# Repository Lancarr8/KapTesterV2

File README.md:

# ⚡ KapTester V2

> Capacitance Tester — ATmega328P based custom PCB project  
> Built as **AP2 (Abschlussprüfung Teil 2)** — Vocational exam project 🇩🇪

---

## 📷 Photos
*Coming soon – V2 build photos*

---

## 📖 About

The **KapTester V2** is a custom-built capacitance measurement device based on the ATmega328P microcontroller. It was designed and built from scratch as part of a vocational training exam (IHK AP2), covering all phases from schematic design to PCB manufacturing and firmware development.

---

## ⚙️ Hardware

| Component | Details |
|-----------|---------|
| MCU | ATmega328P @ 16MHz |
| Display | SSD1306 OLED 128x64 (I2C) |
| Voltage Reg | LM317 (1.2V – 32V adjustable) |
| PCB | Custom 2-layer, manufactured by PCBWay |
| Power | USB (5V) |
| Interface | Tactile button, screw terminals |

---

## 💾 Firmware

Three firmware versions were developed during the project:

| Version | Folder | Description |
|---------|--------|-------------|
| FW1 | `fw1_produktion` | Production firmware – stable release |
| FW2 | `fw2_test` | Test firmware – debugging & measurement testing |
| FW3 | `fw3_Voll` | Full feature firmware – all functions enabled |

### 🔧 Flashing

```bash
# Flash production firmware via avrdude
avrdude -c usbasp -p m328p -U flash:w:fw1_produktion/kaptester.hex:i
```

---

## 📁 Repository Structure

```
KapTesterV2/
├── Firmware/
│   ├── fw1_produktion/     # Production firmware (main.c, .hex, .elf)
│   ├── fw2_test/           # Test firmware
│   └── fw3_Voll/           # Full firmware
├── KiCad KapTester V2/
│   ├── KapTesterV2.kicad_sch   # Schematic
│   ├── KapTesterV2.kicad_pcb   # PCB layout
│   └── GerberV2/               # Gerber files for manufacturing
├── Dokumente/              # Project documentation (German)
│   └── Phasen/             # Phase documentation (Info/Plan/Build/Evaluate)
└── Präsentation/           # Final exam presentation (PPTX + PDF)
```

---

## 🛠️ Tools Used

- **AVR-GCC** – Firmware compilation
- **avrdude** – Flashing
- **KiCad 8** – Schematic & PCB design
- **PCBWay** – PCB manufacturing

---

## 📄 License

MIT License – feel free to use, modify and build upon this project.

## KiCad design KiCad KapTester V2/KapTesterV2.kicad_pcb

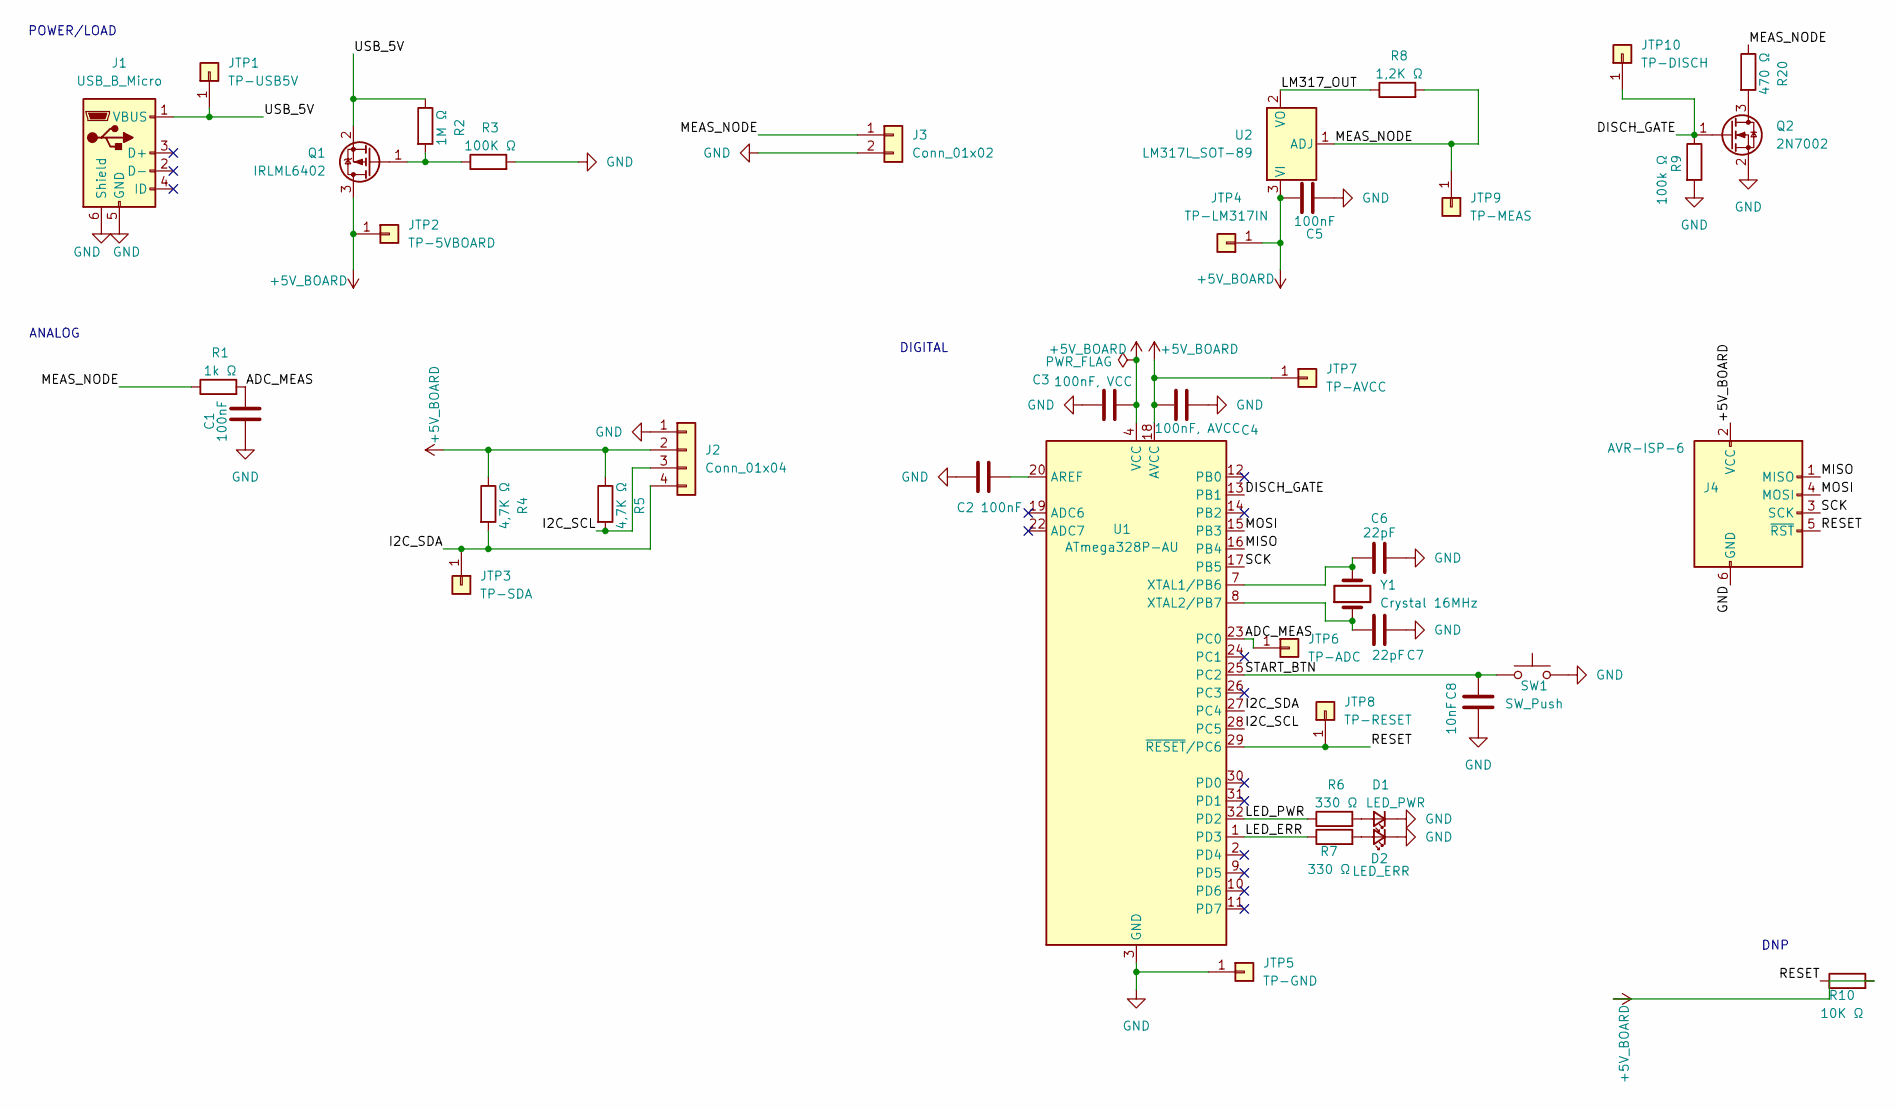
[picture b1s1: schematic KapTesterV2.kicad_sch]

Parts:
C1, C2, C5: 100nF; C_0805_2012Metric_Pad1.18x1.45mm_HandSolder
C3: 100nF, VCC; C_0805_2012Metric_Pad1.18x1.45mm_HandSolder
C4: 100nF, AVCC; C_0805_2012Metric_Pad1.18x1.45mm_HandSolder
C6, C7: 22pF; C_Disc_D3.4mm_W2.1mm_P2.50mm
C8: 10nF; C_0805_2012Metric_Pad1.18x1.45mm_HandSolder
D1: LED_PWR; LED_D5.0mm
D2: LED_ERR; LED_D5.0mm
J1: USB_B_Micro; USB_Micro-B_Molex_47346-0001
J2: Conn_01x04; PinHeader_1x04_P2.54mm_Vertical
J3: Conn_01x02; TerminalBlock_Phoenix_MKDS-1,5-2-5.08_1x02_P5.08mm_Horizont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
J4: AVR-ISP-6; PinHeader_2x03_P2.54mm_Vertical
JTP1: TP-USB5V; PinHeader_1x01_P2.54mm_Vertical
JTP2: TP-5VBOARD; PinHeader_1x01_P2.54mm_Vertical
JTP3: TP-SDA; PinHeader_1x01_P2.54mm_Vertical
JTP4: TP-LM317IN; PinHeader_1x01_P2.54mm_Vertical
JTP5: TP-GND; PinHeader_1x01_P2.54mm_Vertical
JTP6: TP-ADC; PinHeader_1x01_P2.54mm_Vertical
JTP7: TP-AVCC; PinHeader_1x01_P2.54mm_Vertical
JTP8: TP-RESET; PinHeader_1x01_P2.54mm_Vertical
JTP9: TP-MEAS; PinHeader_1x01_P2.54mm_Vertical
JTP10: TP-DISCH; PinHeader_1x01_P2.54mm_Vertical
Q1: IRLML6402; SOT-23
Q2: 2N7002; SOT-23
R1: 1k Ω; R_0805_2012Metric_Pad1.20x1.40mm_HandSolder
R2: 1M Ω; R_MELF_MMB-0207
R3: 100K Ω; R_MELF_MMB-0207
R4, R5: 4,7K Ω; R_0805_2012Metric_Pad1.20x1.40mm_HandSolder
R6, R7: 330 Ω; R_MELF_MMB-0207
R8: 1,2K Ω; R_Axial_DIN0207_L6.3mm_D2.5mm_P7.62mm_Horizontal
R9: 100k Ω; R_Axial_DIN0207_L6.3mm_D2.5mm_P7.62mm_Horizontal
R10: 10K Ω; R_Axial_DIN0207_L6.3mm_D2.5mm_P7.62mm_Horizontal
R20: 470 Ω; R_0805_2012Metric_Pad1.20x1.40mm_HandSolder
SW1: SW_Push; SW_PUSH_6mm_H5mm
U1: ATmega328P-AU; TQFP-32_7x7mm_P0.8mm
U2: LM317L_SOT-89; SOT-89-3
Y1: Crystal 16MHz; Crystal_HC49-U_Vertical

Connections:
+5V_BOARD: C3.2, C4.2, C5.2, J2.2, J4.2 (VCC), JTP2.1, JTP4.1, JTP7.1, Q1.3 (D), R4.1, R5.1, R10.2, U1.4 (VCC), U1.6 (VCC), U1.18 (AVCC), U2.3 (VI)
/ADC_MEAS: C1.2, JTP6.1, R1.2, U1.23 (PC0)
/DISCH_GATE: JTP10.1, Q2.1 (G), R9.1, U1.13 (PB1)
/I2C_SCL: J2.3, R5.2, U1.28 (PC5)
/I2C_SDA: J2.4, JTP3.1, R4.2, U1.27 (PC4)
/LED_ERR: R7.1, U1.1 (PD3)
/LED_PWR: R6.1, U1.32 (PD2)
/LM317_OUT: R8.1, U2.2 (VO)
/MEAS_NODE: J3.1, JTP9.1, R1.1, R8.2, R20.1, U2.1 (ADJ)
/MISO: J4.1 (MISO), U1.16 (PB4)
/MOSI: J4.4 (MOSI), U1.15 (PB3)
/RESET: J4.5 (~RST), JTP8.1, R10.1, U1.29 (~RESET/PC6)
/SCK: J4.3 (SCK), U1.17 (PB5)
/START_BTN: C8.1, SW1.1, U1.25 (PC2)
/USB_5V: J1.1 (VBUS), JTP1.1, Q1.2 (S), R2.1
GND: C1.1, C2.1, C3.1, C4.1, C5.1, C6.2, C7.1, C8.2, D1.1 (K), D2.1 (K), J1.5 (GND), J1.6 (Shield), J2.1, J3.2, J4.6 (GND), JTP5.1, Q2.2 (S), R3.2, R9.2, SW1.2, U1.3 (GND), U1.5 (GND), U1.21 (GND)
unnamed: D1.2 (A), R6.2
unnamed: D2.2 (A), R7.2
unnamed: Q1.1 (G), R2.2, R3.1
unnamed: Q2.3 (D), R20.2
unnamed: C2.2, U1.20 (AREF)
unnamed: C6.1, U1.7 (XTAL1/PB6), Y1.2
unnamed: C7.2, U1.8 (XTAL2/PB7), Y1.1

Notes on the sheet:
ANALOG
POWER/LOAD
DIGITAL
DNP

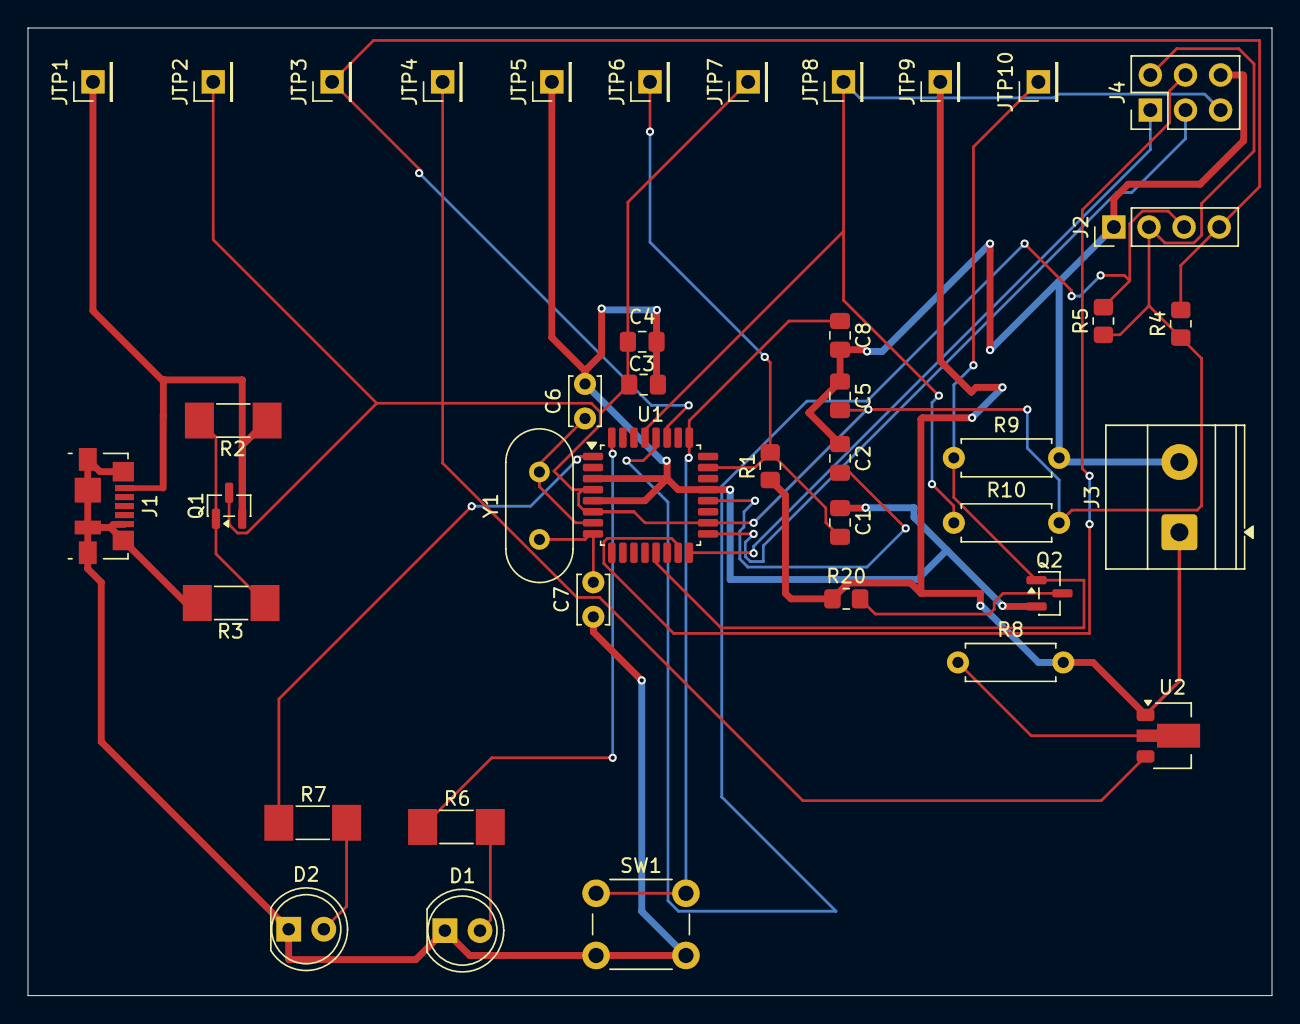
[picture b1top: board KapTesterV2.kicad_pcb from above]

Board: 2 copper layers, 90.0 x 70.0 mm, 41 parts (0 on the bottom side), 23 nets.

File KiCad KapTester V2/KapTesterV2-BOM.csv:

"Reference","Qty","Value","DNP","Exclude from BOM","Exclude from Board","Footprint","Datasheet"
"C1,C2,C5","3","100nF","","","","Capacitor_SMD:C_0805_2012Metric_Pad1.18x1.45mm_HandSolder","~"
"C3","1","100nF, VCC","","","","Capacitor_SMD:C_0805_2012Metric_Pad1.18x1.45mm_HandSolder","~"
"C4","1","100nF, AVCC","","","","Capacitor_SMD:C_0805_2012Metric_Pad1.18x1.45mm_HandSolder","~"
"C6,C7","2","22pF","","","","Capacitor_THT:C_Disc_D3.4mm_W2.1mm_P2.50mm","~"
"C8","1","10nF","","","","Capacitor_SMD:C_0805_2012Metric_Pad1.18x1.45mm_HandSolder","~"
"D1","1","LED_PWR","","","","LED_THT:LED_D5.0mm","~"
"D2","1","LED_ERR","","","","LED_THT:LED_D5.0mm","~"
"J1","1","USB_B_Micro","","","","Connector_USB:USB_Micro-B_Molex_47346-0001","~"
"J2","1","Conn_01x04","","","","Connector_PinHeader_2.54mm:PinHeader_1x04_P2.54mm_Vertical","~"
"J3","1","Conn_01x02","","","","TerminalBlock_Phoenix:TerminalBlock_Phoenix_MKDS-1,5-2-5.08_1x02_P5.08mm_Horizontal","~"
"J4","1","AVR-ISP-6","","","","Connector_PinHeader_2.54mm:PinHeader_2x03_P2.54mm_Vertical","~"
"JTP1","1","TP-USB5V","","","","Connector_PinHeader_2.54mm:PinHeader_1x01_P2.54mm_Vertical","~"
"JTP2","1","TP-5VBOARD","","","","Connector_PinHeader_2.54mm:PinHeader_1x01_P2.54mm_Vertical","~"
"JTP3","1","TP-SDA","","","","Connector_PinHeader_2.54mm:PinHeader_1x01_P2.54mm_Vertical","~"
"JTP4","1","TP-LM317IN","","","","Connector_PinHeader_2.54mm:PinHeader_1x01_P2.54mm_Vertical","~"
"JTP5","1","TP-GND","","","","Connector_PinHeader_2.54mm:PinHeader_1x01_P2.54mm_Vertical","~"
"JTP6","1","TP-ADC","","","","Connector_PinHeader_2.54mm:PinHeader_1x01_P2.54mm_Vertical","~"
"JTP7","1","TP-AVCC","","","","Connector_PinHeader_2.54mm:PinHeader_1x01_P2.54mm_Vertical","~"
"JTP8","1","TP-RESET","","","","Connector_PinHeader_2.54mm:PinHeader_1x01_P2.54mm_Vertical","~"
"JTP9","1","TP-MEAS","","","","Connector_PinHeader_2.54mm:PinHeader_1x01_P2.54mm_Vertical","~"
"JTP10","1","TP-DISCH","","","","Connector_PinHeader_2.54mm:PinHeader_1x01_P2.54mm_Vertical","~"
"Q1","1","IRLML6402","","","","Package_TO_SOT_SMD:SOT-23","https://www.infineon.com/dgdl/irlml6402pbf.pdf?fileId=5546d4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"
"Q2","1","2N7002","","","","Package_TO_SOT_SMD:SOT-23","https://www.onsemi.com/pub/Collateral/NDS7002A-D.PDF"
"R1","1","1k Ω","","","","Resistor_THT:R_Axial_DIN0207_L6.3mm_D2.5mm_P7.62mm_Horizontal","~"
"R2,R3","2","100K Ω","","","","Resistor_SMD:R_MELF_MMB-0207","~"
"R4,R5","2","4,7K Ω","","","","Resistor_SMD:R_0805_2012Metric_Pad1.20x1.40mm_HandSolder","~"
"R6,R7","2","330 Ω","","","","Resistor_SMD:R_MELF_MMB-0207","~"
"R8","1","1,2K Ω","","","","Resistor_THT:R_Axial_DIN0207_L6.3mm_D2.5mm_P7.62mm_Horizontal","~"
"R9","1","100k Ω","","","","Resistor_THT:R_Axial_DIN0207_L6.3mm_D2.5mm_P7.62mm_Horizontal","~"
"R10","1","10K Ω","","","","Resistor_THT:R_Axial_DIN0207_L6.3mm_D2.5mm_P7.62mm_Horizontal","~"
"SW1","1","SW_Push","","","","Button_Switch_THT:SW_PUSH_6mm_H5mm","~"
"U1","1","ATmega328P-AU","","","","Package_QFP:TQFP-32_7x7mm_P0.8mm","http://ww1.microchip.com/downloads/en/DeviceDoc/ATmega328_P%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"
"U2","1","LM317L_SOT-89","","","","Package_TO_SOT_SMD:SOT-89-3","http://www.ti.com/lit/ds/symlink/lm317l.pdf"
"Y1","1","Crystal 16MHz","","","","Crystal:Crystal_HC49-U_Vertical","~"

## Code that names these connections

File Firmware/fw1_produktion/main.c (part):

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/* ═══════════════════════════════════════════════════════════════════════
 * HARDWARE-ABSTRAKTION (GPIO-MAKROS NACH DATENBLATT)
 * ═══════════════════════════════════════════════════════════════════════ */
#define LED_GRN_ON()    (PORTD |=  (1<<PD2))  /* Grüne LED aktivieren (High-Pegel)  */
#define LED_GRN_OFF()   (PORTD &= ~(1<<PD2))  /* Grüne LED deaktivieren (Low-Pegel) */
#define LED_RED_ON()    (PORTD |=  (1<<PD3))  /* Rote LED aktivieren (High-Pegel)   */
#define LED_RED_OFF()   (PORTD &= ~(1<<PD3))  /* Rote LED deaktivieren (Low-Pegel)  */
#define DISCH_ON()      (PORTB |=  (1<<PB1))  /* Entlade-MOSFET durchschalten       */
#define DISCH_OFF()     (PORTB &= ~(1<<PB1))  /* Entlade-MOSFET sperren             */
#define BTN_PRESSED()   (!(PINC & (1<<PC2)))  /* Taster gegen Masse abfragen (Low-aktiv) */

/*
 * MAKRO: ANALOG-DIGITAL-WANDLER RESTAURIEREN
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
// GPIO-Richtungsregister initialisieren
void gpio_init(void) {
    DDRD |=  (1<<PD2) | (1<<PD3);  /* PD2 (LED_GRN) und PD3 (LED_RED) als Ausgang definieren */
    DDRB |=  (1<<PB1);             /* PB1 (DISCH_GATE) als digitalen Ausgang definieren       */
    DDRC &= ~((1<<PC2) | (1<<PC0));/* PC2 (Button) und PC0 (ADC-Messkanal) als Eingang       */
    PORTC |=  (1<<PC2);            /* Internen Pull-Up-Widerstand für den Taster aktivieren    */
    PORTC &= ~(1<<PC0);            /* Pull-Up für analogen Messkanal deaktivieren (hochohmig)  */
    LED_GRN_OFF(); LED_RED_OFF(); DISCH_OFF(); /* Sicheren Ausgangszustand erzwingen */
}

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
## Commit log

2026-05-24 Initial commit – KapTester V2 AP2 Project
2026-05-24 Remove private documents and receipts
2026-05-24 Improve README with badges and structure
